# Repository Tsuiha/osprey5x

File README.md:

# osprey5x
50% rowstaggered keyboard

QMK Fimware, [OSPREY 5X codes](https://github.com/Tsuiha/vial-qmk/tree/vial/keyboards/0_tsuiha/osprey5x)

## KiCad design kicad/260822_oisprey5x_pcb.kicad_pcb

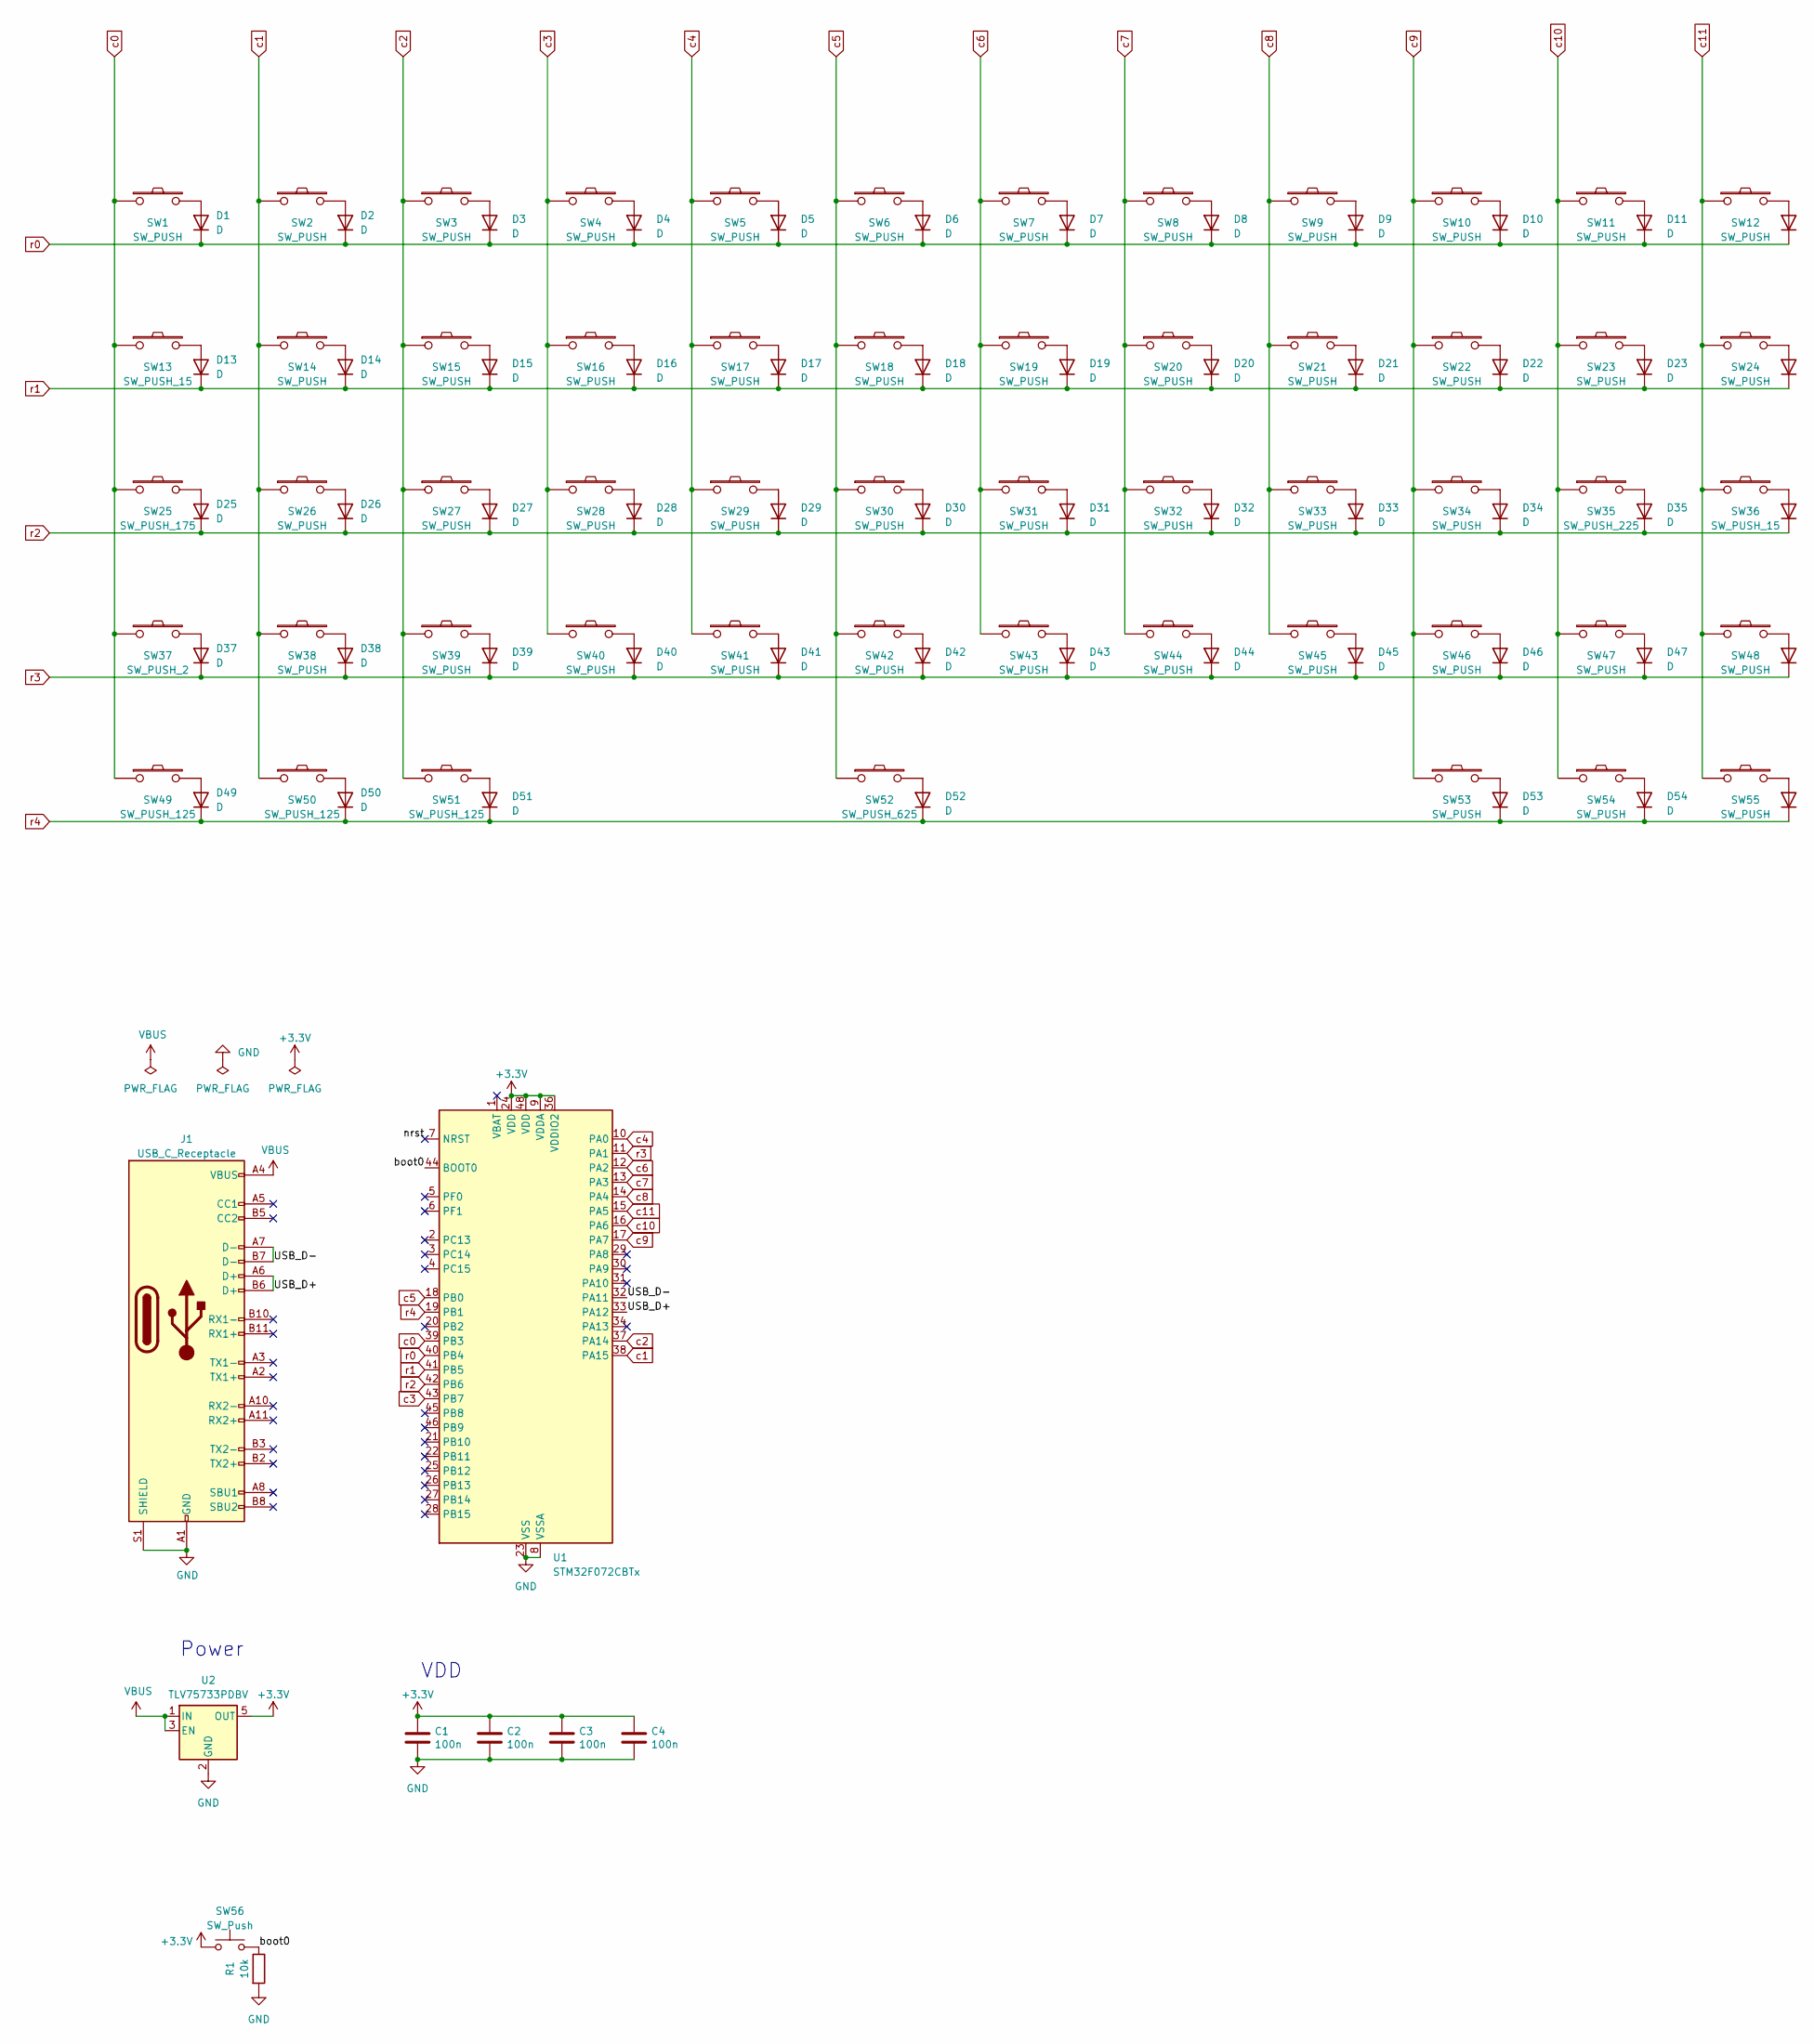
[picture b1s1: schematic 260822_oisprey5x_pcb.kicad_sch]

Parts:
C1, C2, C3, C4: 100n; C_0603_1608Metric
D1, D2, D3, D4, D5, D6, D7, D8, D9, D10, D11, D12, D13, D14, D15, D16, D17, D18, D19, D20, D21, D22, D23, D24, D25, D26, D27, D28, D29, D30, D31, D32, D33, D34, D35, D36, D37, D38, D39, D40, D41, D42, D43, D44, D45, D46, D47, D48, D49, D50, D51, D52, D53, D54, D55: D; Diode_SMD_noname
J1: USB_C_Receptacle; USB_C_Receptacle_HRO_TYPE-C-31-M-12_My
R1: 10k; C_0603_1608Metric
SW1, SW2, SW3, SW4, SW5, SW6, SW7, SW8, SW9, SW10, SW11, SW12, SW14, SW15, SW16, SW17, SW18, SW19, SW20, SW21, SW22, SW23, SW24, SW26, SW27, SW28, SW29, SW30, SW31, SW32, SW33, SW34, SW38, SW39, SW40, SW41, SW42, SW43, SW44, SW45, SW46, SW47, SW48, SW53, SW54, SW55: SW_PUSH; GLPV3_1U
SW13, SW36: SW_PUSH_15; GLPV3_1.5U
SW25: SW_PUSH_175; GLPV3_1.75U
SW35: SW_PUSH_225; GLPV3_2.25u_r
SW37: SW_PUSH_2; GLPV3_2u_r
SW49, SW50, SW51: SW_PUSH_125; GLPV3_1.25U
SW52: SW_PUSH_625; GLPV3_6.25u_r
SW56: SW_Push; SW_SPST_SKQG_WithStem
U1: STM32F072CBTx; LQFP-48_7x7mm_P0.5mm
U2: TLV75733PDBV; SOT-23-5

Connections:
+3.3V: C1.1, C2.1, C3.1, C4.1, SW56.1, U1.9 (VDDA), U1.24 (VDD), U1.36 (VDDIO2), U1.48 (VDD), U2.5 (OUT)
/USB_D+: J1.A6 (D+), J1.B6 (D+), U1.33 (PA12)
/USB_D-: J1.A7 (D-), J1.B7 (D-), U1.32 (PA11)
/boot0: R1.1, SW56.2, U1.44 (BOOT0)
/nrst: U1.7 (NRST)
GND: C1.2, C2.2, C3.2, C4.2, J1.A1 (GND), J1.A12 (GND), J1.B1 (GND), J1.B12 (GND), J1.S1 (SHIELD), R1.2, U1.8 (VSSA), U1.23 (VSS), U1.35 (VSS), U1.47 (VSS), U2.2 (GND)
unnamed: D1.2 (A), SW1.2
unnamed: D2.2 (A), SW2.2
unnamed: D3.2 (A), SW3.2
unnamed: D4.2 (A), SW4.2
unnamed: D5.2 (A), SW5.2
unnamed: D6.2 (A), SW6.2
unnamed: D7.2 (A), SW7.2
unnamed: D8.2 (A), SW8.2
unnamed: D9.2 (A), SW9.2
unnamed: D10.2 (A), SW10.2
unnamed: D11.2 (A), SW11.2
unnamed: D12.2 (A), SW12.2
unnamed: D13.2 (A), SW13.2
unnamed: D14.2 (A), SW14.2
unnamed: D15.2 (A), SW15.2
unnamed: D16.2 (A), SW16.2
unnamed: D17.2 (A), SW17.2
unnamed: D18.2 (A), SW18.2
unnamed: D19.2 (A), SW19.2
unnamed: D20.2 (A), SW20.2
unnamed: D21.2 (A), SW21.2
unnamed: D22.2 (A), SW22.2
unnamed: D23.2 (A), SW23.2
unnamed: D24.2 (A), SW24.2
unnamed: D25.2 (A), SW25.2
unnamed: D26.2 (A), SW26.2
unnamed: D27.2 (A), SW27.2
unnamed: D28.2 (A), SW28.2
unnamed: D29.2 (A), SW29.2
unnamed: D30.2 (A), SW30.2
unnamed: D31.2 (A), SW31.2
unnamed: D32.2 (A), SW32.2
unnamed: D33.2 (A), SW33.2
unnamed: D34.2 (A), SW34.2
unnamed: D35.2 (A), SW35.2
unnamed: D36.2 (A), SW36.2
unnamed: D37.2 (A), SW37.2
unnamed: D38.2 (A), SW38.2
unnamed: D39.2 (A), SW39.2
unnamed: D40.2 (A), SW40.2
unnamed: D41.2 (A), SW41.2
unnamed: D42.2 (A), SW42.2
unnamed: D43.2 (A), SW43.2
unnamed: D44.2 (A), SW44.2
unnamed: D45.2 (A), SW45.2
unnamed: D46.2 (A), SW46.2
unnamed: D47.2 (A), SW47.2
unnamed: D48.2 (A), SW48.2
unnamed: D49.2 (A), SW49.2
unnamed: D50.2 (A), SW50.2
unnamed: D51.2 (A), SW51.2
unnamed: D52.2 (A), SW52.2
unnamed: D53.2 (A), SW53.2
unnamed: D54.2 (A), SW54.2
unnamed: D55.2 (A), SW55.2
VBUS: J1.A4 (VBUS), J1.A9 (VBUS), J1.B4 (VBUS), J1.B9 (VBUS), U2.1 (IN), U2.3 (EN)
c0: SW1.1, SW13.1, SW25.1, SW37.1, SW49.1, U1.39 (PB3)
c1: SW2.1, SW14.1, SW26.1, SW38.1, SW50.1, U1.38 (PA15)
c2: SW3.1, SW15.1, SW27.1, SW39.1, SW51.1, U1.37 (PA14)
c3: SW4.1, SW16.1, SW28.1, SW40.1, U1.43 (PB7)
c4: SW5.1, SW17.1, SW29.1, SW41.1, U1.10 (PA0)
c5: SW6.1, SW18.1, SW30.1, SW42.1, SW52.1, U1.18 (PB0)
c6: SW7.1, SW19.1, SW31.1, SW43.1, U1.12 (PA2)
c7: SW8.1, SW20.1, SW32.1, SW44.1, U1.13 (PA3)
c8: SW9.1, SW21.1, SW33.1, SW45.1, U1.14 (PA4)
c9: SW10.1, SW22.1, SW34.1, SW46.1, SW53.1, U1.17 (PA7)
c10: SW11.1, SW23.1, SW35.1, SW47.1, SW54.1, U1.16 (PA6)
c11: SW12.1, SW24.1, SW36.1, SW48.1, SW55.1, U1.15 (PA5)
r0: D1.1 (K), D2.1 (K), D3.1 (K), D4.1 (K), D5.1 (K), D6.1 (K), D7.1 (K), D8.1 (K), D9.1 (K), D10.1 (K), D11.1 (K), D12.1 (K), U1.40 (PB4)
r1: D13.1 (K), D14.1 (K), D15.1 (K), D16.1 (K), D17.1 (K), D18.1 (K), D19.1 (K), D20.1 (K), D21.1 (K), D22.1 (K), D23.1 (K), D24.1 (K), U1.41 (PB5)
r2: D25.1 (K), D26.1 (K), D27.1 (K), D28.1 (K), D29.1 (K), D30.1 (K), D31.1 (K), D32.1 (K), D33.1 (K), D34.1 (K), D35.1 (K), D36.1 (K), U1.42 (PB6)
r3: D37.1 (K), D38.1 (K), D39.1 (K), D40.1 (K), D41.1 (K), D42.1 (K), D43.1 (K), D44.1 (K), D45.1 (K), D46.1 (K), D47.1 (K), D48.1 (K), U1.11 (PA1)
r4: D49.1 (K), D50.1 (K), D51.1 (K), D52.1 (K), D53.1 (K), D54.1 (K), D55.1 (K), U1.19 (PB1)

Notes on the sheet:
Power
VDD

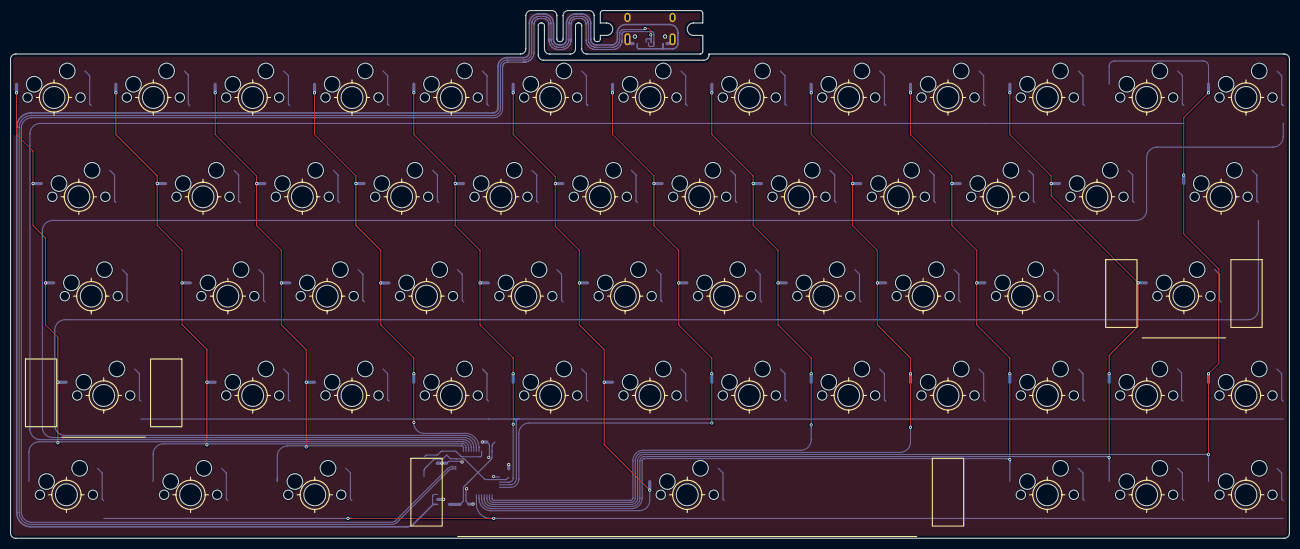
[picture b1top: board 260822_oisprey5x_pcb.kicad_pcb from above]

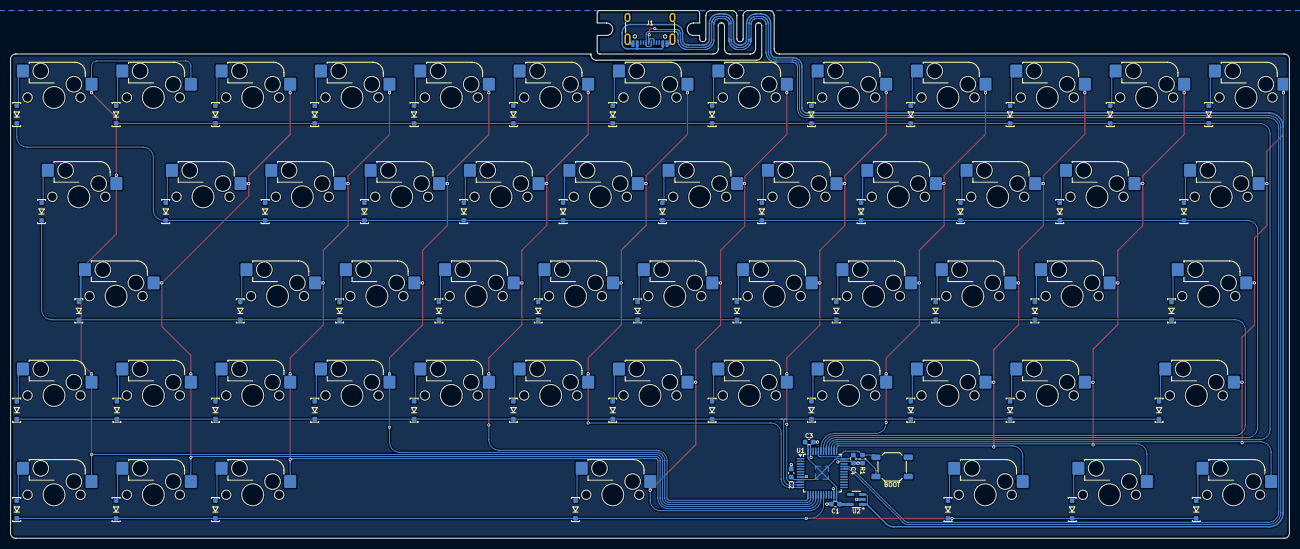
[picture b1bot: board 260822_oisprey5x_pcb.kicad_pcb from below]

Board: 2 copper layers, 245.3 x 101.2 mm, 119 parts (9 on the bottom side), 78 nets.
